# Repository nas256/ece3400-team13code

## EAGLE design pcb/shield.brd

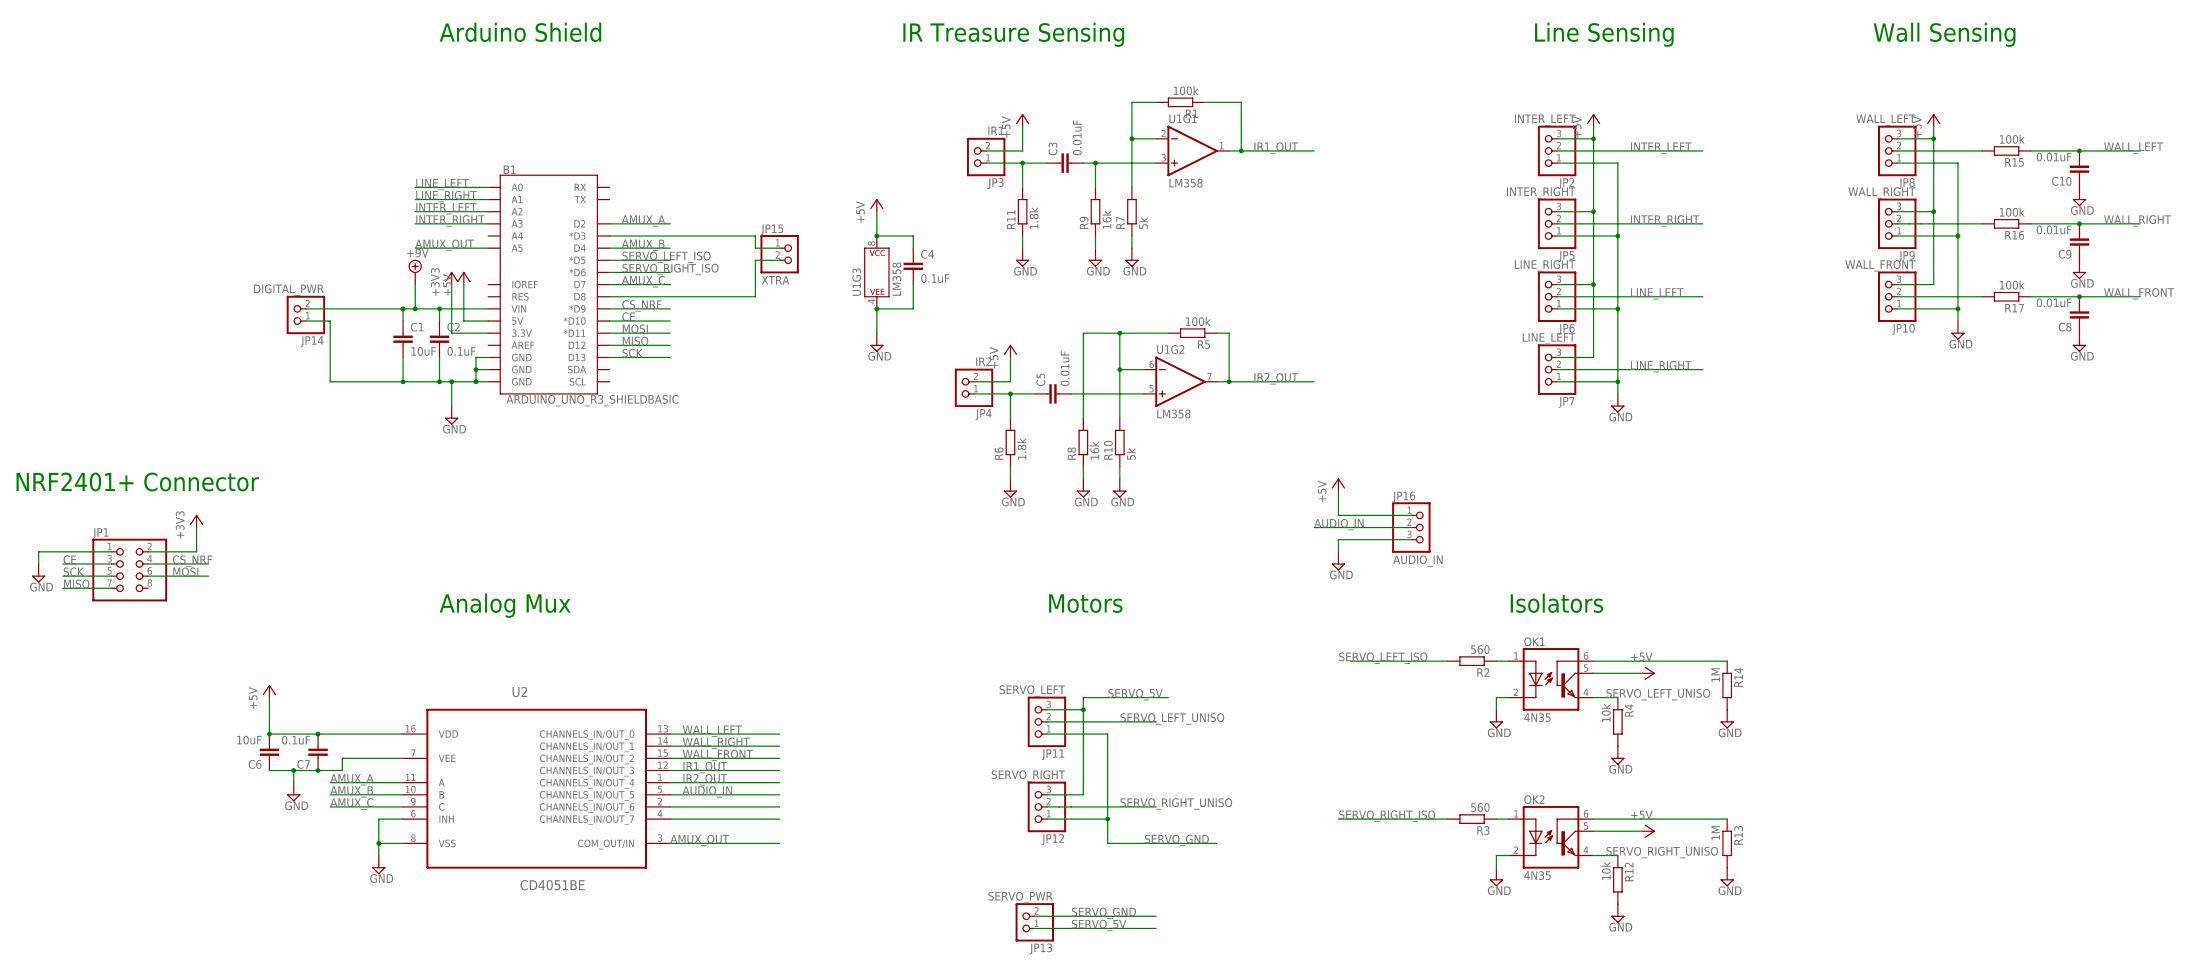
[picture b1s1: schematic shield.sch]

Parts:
B1: ARDUINO_UNO_R3_SHIELDBASIC; UNO_R3_SHIELD
C1, C6: 10uF; C5B3
C2, C7: 0.1uF; C5B3
C3, C5, C8, C9, C10: 0.01uF; C5B3
C4: 0.1uF; C2.5-2
JP1: PINHD-2X4; 2X04
JP2: INTER_LEFT; 1X03
JP3: IR1; 1X02
JP4: IR2; 1X02
JP5: INTER_RIGHT; 1X03
JP6: LINE_RIGHT; 1X03
JP7: LINE_LEFT; 1X03
JP8: WALL_LEFT; 1X03
JP9: WALL_RIGHT; 1X03
JP10: WALL_FRONT; 1X03
JP11: SERVO_LEFT; 1X03
JP12: SERVO_RIGHT; 1X03
JP13: SERVO_PWR; 1X02
JP14: DIGITAL_PWR; 1X02
JP15: XTRA; 1X02
JP16: AUDIO_IN; 1X03
OK1, OK2: 4N35; DIL06
R1, R5, R15, R16, R17: 100k; VMTA55
R2, R3: 560; VMTA55
R4, R12: 10k; VMTA55
R6, R11: 1.8k; VMTA55
R7, R10: 5k; VMTA55
R8, R9: 16k; VMTA55
R13, R14: 1M; VMTA55
U1: LM358; DIP08
U2: CD4051BE; DIP254P762X508-16

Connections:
+3V3: B1.3.3V, JP1.2
+5V: B1.5V, C4.1, C6.2, C7.2, JP2.3, JP3.2, JP4.2, JP5.3, JP6.3, JP7.3, JP8.3, JP9.3, JP10.3, JP16.1, OK1.5 (COL), OK2.5 (COL), U1.8 (P$V+), U2.16 (VDD)
AMUX_A: B1.D2, U2.11 (A)
AMUX_B: B1.D4, U2.10 (B)
AMUX_C: B1.D7, U2.9 (C)
AMUX_OUT: B1.A5, U2.3 (COM_OUT/IN)
AUDIO_IN: JP16.2, U2.5 (CHANNELS_IN/OUT_5)
CE: B1.D10 (*D10), JP1.3
CS_NRF: B1.D9 (*D9), JP1.4
GND: B1.GND@0 (GND), B1.GND@1 (GND), B1.GND@2 (GND), C1.2, C2.2, C4.2, C6.1, C7.1, C8.1, C9.1, C10.1, JP1.1, JP2.1, JP5.1, JP6.1, JP7.1, JP8.1, JP9.1, JP10.1, JP14.1, JP16.3, OK1.2 (C), OK2.2 (C), R4.2, R6.1, R7.1, R8.1, R9.1, R10.1, R11.1, R12.2, R13.2, R14.2, U1.4 (P$V-), U2.6 (INH), U2.7 (VEE), U2.8 (VSS)
INTER_LEFT: B1.A2, JP2.2
INTER_RIGHT: B1.A3, JP5.2
IR1_OUT: R1.1, U1.1 (OUT), U2.12 (CHANNELS_IN/OUT_3)
IR2_OUT: R5.1, U1.7 (OUT), U2.1 (CHANNELS_IN/OUT_4)
LINE_LEFT: B1.A0, JP6.2
LINE_RIGHT: B1.A1, JP7.2
MISO: B1.D12, JP1.7
MOSI: B1.D11 (*D11), JP1.6
unnamed: C3.1, JP3.1, R11.2
unnamed: B1.VIN, C1.1, C2.1, JP14.2
unnamed: C3.2, R9.2, U1.3 (+IN)
unnamed: R1.2, R7.2, U1.2 (-IN)
unnamed: C5.1, JP4.1, R6.2
unnamed: C5.2, U1.5 (+IN)
unnamed: R5.2, R8.2, R10.2, U1.6 (-IN)
unnamed: OK1.6 (BAS), R14.1
unnamed: B1.D3 (*D3), JP15.1
unnamed: OK2.1 (A), R3.1
unnamed: OK1.1 (A), R2.1
unnamed: B1.D8, JP15.2
unnamed: JP8.2, R15.2
unnamed: OK2.6 (BAS), R13.1
unnamed: JP9.2, R16.2
unnamed: JP10.2, R17.2
SCK: B1.D13, JP1.5
SERVO_5V: JP11.3, JP12.3, JP13.1
SERVO_GND: JP11.1, JP12.1, JP13.2
SERVO_LEFT_ISO: B1.D5 (*D5), R2.2
SERVO_LEFT_UNISO: JP11.2, OK1.4 (EMI), R4.1
SERVO_RIGHT_ISO: B1.D6 (*D6), R3.2
SERVO_RIGHT_UNISO: JP12.2, OK2.4 (EMI), R12.1
WALL_FRONT: C8.2, R17.1, U2.15 (CHANNELS_IN/OUT_2)
WALL_LEFT: C10.2, R15.1, U2.13 (CHANNELS_IN/OUT_0)
WALL_RIGHT: C9.2, R16.1, U2.14 (CHANNELS_IN/OUT_1)

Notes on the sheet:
IR Treasure Sensing
Line Sensing
Wall Sensing
Arduino Shield
Analog Mux
Motors
Isolators
NRF2401+ Connector

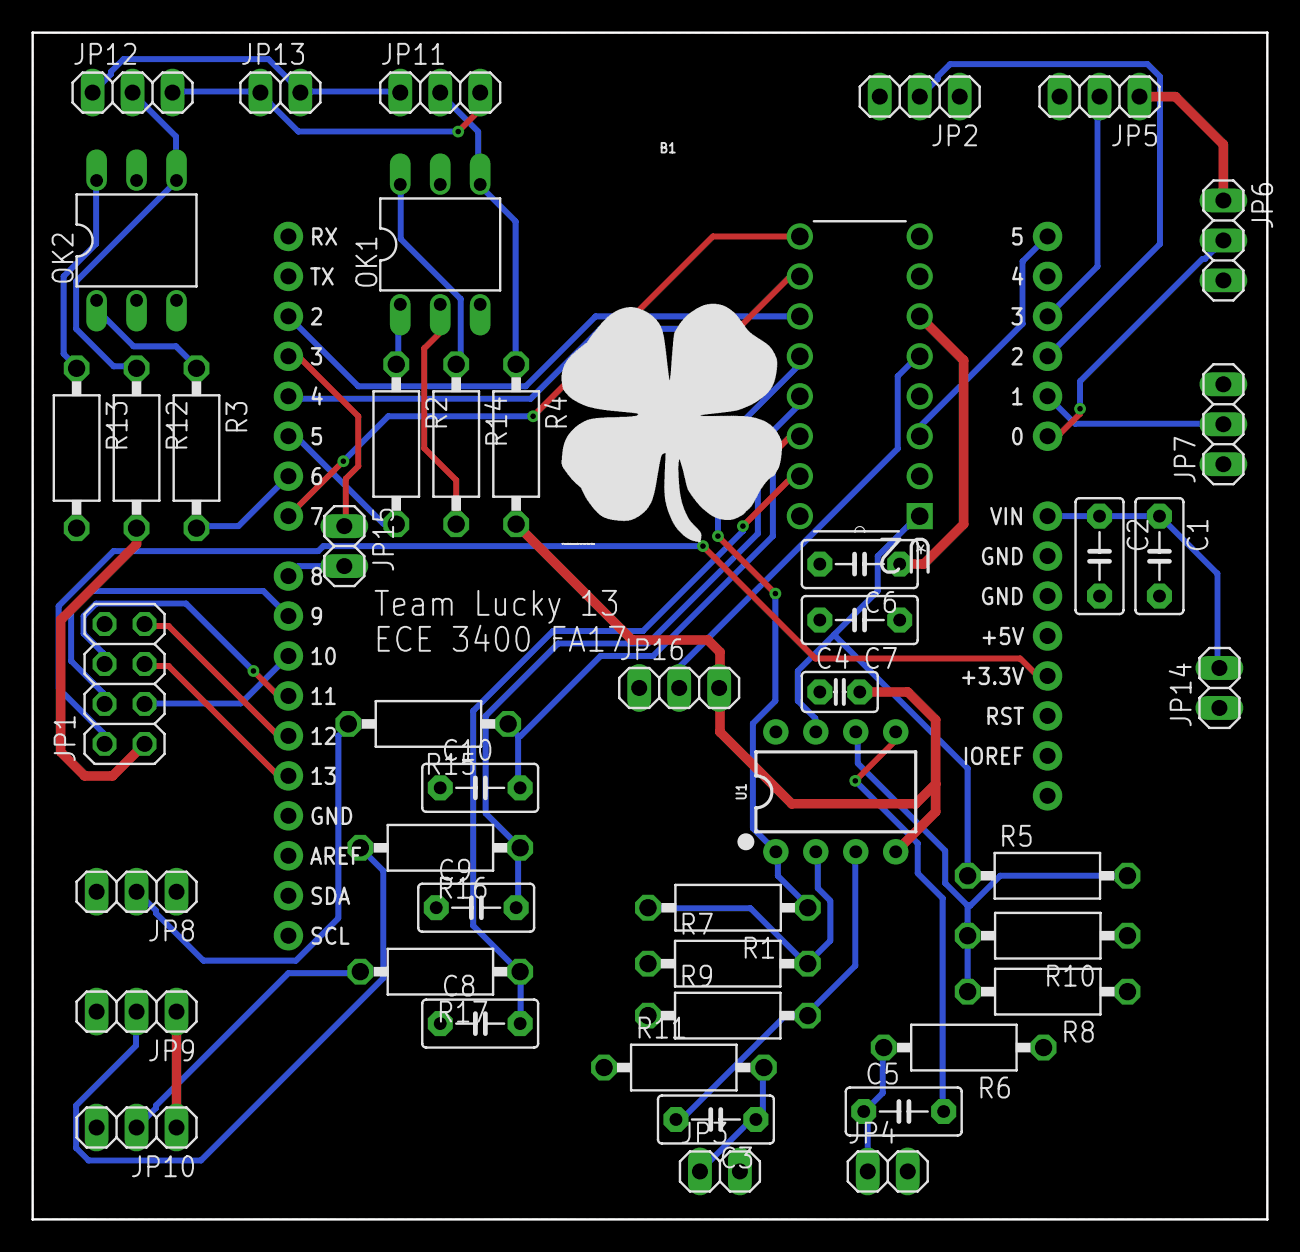
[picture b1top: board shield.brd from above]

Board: 2 copper layers, 78.5 x 75.4 mm, 48 parts (0 on the bottom side), 44 nets.

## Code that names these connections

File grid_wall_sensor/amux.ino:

#include "amux.h"

void amux_init(void){
  // Initializes outputs
  pinMode(AMUX_A, OUTPUT);
  pinMode(AMUX_B, OUTPUT);
  pinMode(AMUX_C, OUTPUT);

  // If using the enable pin, enable it as an output
  // and enable the mux
  #ifdef AMUX_USE_ENABLE
  pinMode(AMUX_EN, OUTPUT);
  amux_enable();
  #endif
  
  amux_select(0); // Start off at first input
}

void amux_select(char mux_input){
  // Update each pin according to the mux_input (0-7)
  digitalWrite(AMUX_A, mux_input & (1<<0) ? HIGH : LOW);
  digitalWrite(AMUX_B, mux_input & (1<<1) ? HIGH : LOW);
  digitalWrite(AMUX_C, mux_input & (1<<2) ? HIGH : LOW);
}

#ifdef USE_ENABLE_PIN

void amux_enable(void){
  digitalWrite(AMUX_A, LOW);
}

void amux_disable(void){
  digitalWrite(AMUX_A, HIGH);
}

#endif

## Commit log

2017-09-08 Add line follower code and grid follower code
2017-09-16 Before adding debounce code
2017-09-16 Add code to drive in a figure 8 (grid_follower) and to distinguish 7 vs. 12 kHz IR beacons
2017-09-19 Added fft_merged.ino for lab2 merged code
2017-09-22 Basic wall detection: sense wall and turn right
2017-09-22 Add code to control analog mux (amux.ino/.h)
2017-09-26 Add lab3 verilog template project
2017-09-29 Added FFT optical sketch with LED for milestone 2
2017-09-29 Lotsa stuff: recalibrate robot for shorted servo mounts, add verilog code to display a grid based off memory array
2017-09-29 Rename visual team folder
2017-10-13 Add VGA dance party demo
2017-10-20 Add support for explored, nonexplored, and current location tiles
2017-10-25 arduino code from 10/19 lab section
    tranverse grid in snake motion
2017-11-03 Add basic wall sensing
2017-11-03 Tune turning a bit
2017-11-04 added 180 turning
2017-11-04 implemented 180 turns
2017-11-05 Unfinished maze exploration
2017-11-05 Comment out dfs code, something's wrong with it
2017-11-05 implemented dfs without done signal
2017-11-05 not working version of done signal
2017-11-10 DFS werks!
2017-11-17 Add pcb
2017-11-17 added rf stuff
2017-11-17 Added IR files and modified fft_merged to test IR functionality and measure time it takes
2017-11-17 changed unsigned ints to chars
2017-11-17 IR is currently commented out, and changed wireless to uint16
2017-11-17 Add wall and done functionality to verilog, simulate with arduino :)
2017-11-17 Add base station to git
2017-11-17 Make maze mapper code update internal maze array and then send out
2017-11-18 Make grid wall sensor run on bot
2017-11-18 end of saturday morning session: it draws...funny... things, but robot is properly communicating with basestation, need to work out walls and origin square, etc.
2017-11-18 updated base_station code
2017-11-18 Move merged_rf_spi from drive to github
2017-11-18 Verilog: flip screen to match robot view
2017-11-19 milestone 4 robot code (t)werkin
2017-11-19 fixed base_station
2017-11-19 Verilog: invert y (todo: include enough bits to use IR)
2017-11-20 Tweak IR stuff
2017-11-20 Fix coordinate system on bot to align with actual competition
2017-11-20 Add IR sensing to verilog and to dummy base station test
2017-11-20 Convert everything to a 4x5 grid
2017-11-21 IR sensing mostly works, will need to play with amp circuit a bit
2017-11-28 only tracks treasure at intersections now
2017-12-01 Update pinout to pcb
2017-12-01 before i fuck with stuff
2017-12-01 dfs works
2017-12-02 If all else fails, revert to this
2017-12-03 Competition code

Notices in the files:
parts and their libraries:
SparkFun-Boards: Licensing: Creative Commons ShareAlike 4.0 International - https://creativecommons.org/licenses/by-sa/4.0
